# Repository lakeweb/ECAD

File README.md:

ECAD - Edit Schematics and PC Boards as well as manage projects and libraries from other CAD software.

So far, there are no editing features. The work is on creating a good foundation for CAD. Being able to handle objects easaly and having the UI in place comes first. VS2017 is required. The older compilers are not capable of building the parsers. MS is always behind the C++ language evolution.

Code of interest:
XMLSettingsStore derived from CSettingsStore and the use of pugixml. Find that in HEWinApp.cpp. I don't care for using the registry to store so much information. It should go in the appddata of the user. This will also make it easier to change profiles around.

pugixml wrapper:
In xml.h. Previously I had been using a crusty and bloated vesrsion of an XML wrapper around TinyXML. Tiny was hiden in that implamentation. It as worked fine for me for many years, but it was time to move on. The objective of this new pugi wrapper is to keep all of pugi exposed. But to make its use as a application database much easier. The use is already sprinkled about this app. It started with the XMLSettingsStore.

12/23/2018
BXL parser moved to lib.
Deleted old spirit::qi code.
Made it so recent file load won't crash on bad paths.
Found a lot of header dependencies beyond the repository fixes and depreciated std::tstring stuff.

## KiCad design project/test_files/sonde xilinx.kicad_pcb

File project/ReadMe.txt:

now using pugi xml...

MIlling and screen drawing................................

Geometry.h
	bases of 2D Cartesian points using
	boost geometry.
	support for transformations, rotations, mirroring, etc...

object.h
	primitive objects for milling and drawing
	a base class: BaseItem and containers use SP_BaseItem
		shared pointers..

Drawing.h
	support for drawing objects.

DrawingObect : top level container for drawing
	wrapper for object_set_t called only ItemSet for now.

ItemSet
	owns asp_obj_vect_t
	which is a vector of shared pointers SP_BaseItem

11/27/2018
	polygons are supported. They can be open, and/or, they can be filled.
	An ItemSet stored as a base object will not be considered a polygon. This may change.
	But if an ItemSet is stored in an ItemSet, it will be treated as a polygon.

	So far, the fill is a 

...........................................................................
The Tiny Parse
...........................................................................
boost::geometry does not support curved lines much less in a line string.
So each polygon is stored on a ItemSet.

			//<POLYGON pos = '15.00000,15.00000' style = '4' fill = '1'>
			//	<POINT pos = '0.00000,0.00000' arc = '0' / >
			//create an object for each polygon to preserve tiny objects.
			//geometry does not support curves in a linestring so....

Note that CppSQLite3U is rather unusable. The only reason it is in here is for tinylib
	it will be updated.....

On the local system, symlinks are set for:
folder: <include/xml.h>
file: <BXLReader/BXL_Component.h>

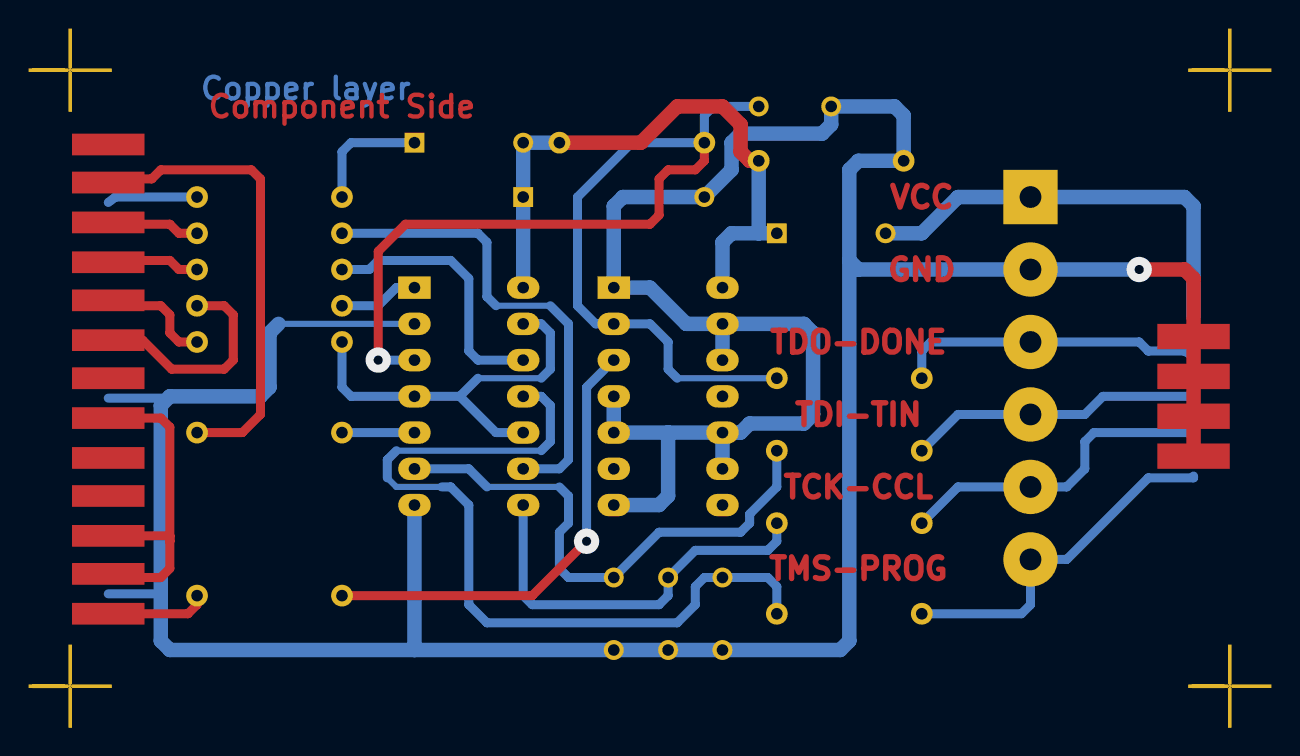
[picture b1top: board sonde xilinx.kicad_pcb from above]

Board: 2 copper layers, 29 parts (0 on the bottom side), 26 nets.

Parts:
C1: 1uF; CP5
C2, C3, C4, C5: 100pF; C2
D1, D2: BAT46; D3
J1: DB25MALE; DB25M_CI
J2: DB9MALE; DB9M_CI_INVERT
MIRE: *; MIRE
MIRE#2, MIRE#3, MIRE#4: *; MIRE
P1: CONN_6; bornier6
R1, R6, R7, R8, R9, R10, R11, R12, R13, R14: 100; R4
R2: 5,1K; R4
R4: 47; R4
R5: 1K; R4
U1, U2: 74LS125; 14DIP-ELL300

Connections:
/CLK-D1: J1.3, R10.2
/CTRL-D3: J1.5, R8.2
/DONE-SELECT*: J1.13, R4.2
/PWR_3,3-5V: D2.1, J2.1, P1.1
/TCK-CCLK: J2.4, P1.5, R12.1
/TD0-DONE: J2.2, P1.3, R14.1
/TD0-PROG-D4: J1.6, R6.2
/TDI-DIN: J2.3, P1.4, R11.1
/TDI-DIN-D0: J1.2, R7.2
/TMS-PROG: J2.5, P1.6, R13.1
/TMS-PROG-D2: J1.4, R9.2
/VCC_SENSE-ERROR*: J1.15, R1.2
GND: C1.2, C2.2, C3.2, C4.2, C5.2, J1.20, J1.25, J2.6, J2.7, J2.8, J2.9, P1.2, R5.2, U1.2, U1.7, U2.1, U2.4, U2.5, U2.7, U2.9, U2.10, U2.12, U2.13
unnamed: J1.8, J1.11, J1.12
unnamed: D1.2, R1.1
unnamed: R4.1, U2.3
unnamed: R7.1, U1.5
unnamed: R10.1, U1.9
unnamed: R6.1, U1.1
unnamed: R9.1, U1.12
unnamed: R8.1, U1.4, U1.10, U1.13
unnamed: C4.1, R13.2, U1.11
unnamed: C2.1, R11.2, U1.6
unnamed: C5.1, R12.2, U1.8
unnamed: C3.1, R2.2, R14.2, U1.3, U2.2
VCC: C1.1, D1.1, D2.2, R2.1, R5.1, U1.14, U2.14

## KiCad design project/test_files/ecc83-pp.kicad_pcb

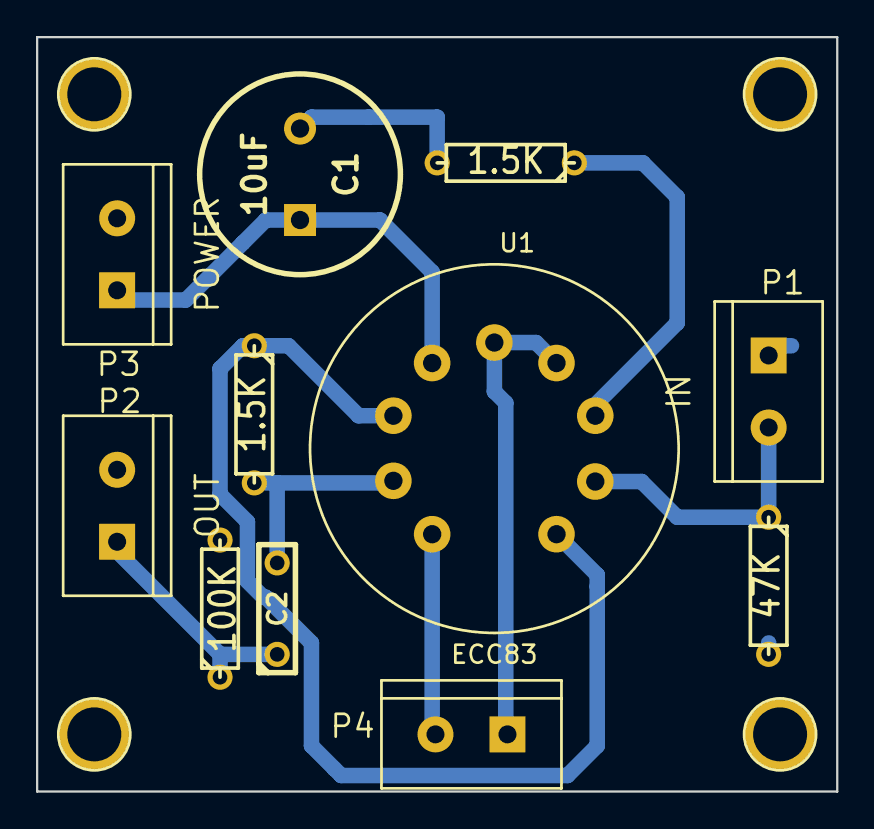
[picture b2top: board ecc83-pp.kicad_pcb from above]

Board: 2 copper layers, 44.5 x 41.9 mm, 15 parts (0 on the bottom side), 9 nets.

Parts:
C1: 10uF; C2V10
C2: 680nF; C2
P1: IN; bornier2
P2: OUT; bornier2
P3: POWER; bornier2
P4: CONN_2; bornier2
P5, P6, P7, P8: CONN_1; 1pin
R1, R2: 1.5K; R3
R3: 100K; R3
R4: 47K; R3
U1: ECC83; VALVE-ECC-83-1

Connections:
GND: C1.2, P1.1, P2.2, P3.2, R2.2, R3.2, R4.2
unnamed: C1.1, P3.1, U1.6
unnamed: C2.1, P2.1, R3.1
unnamed: C2.2, R1.2, U1.8
unnamed: P1.2, R4.1, U1.2
unnamed: P4.1, U1.4, U1.5
unnamed: P4.2, U1.9
unnamed: R1.1, U1.1, U1.7
unnamed: R2.1, U1.3

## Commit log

2018-12-20 First commit
    removing delete
2018-12-21 new file: LICENSE.md modified: README.md
2019-07-27 New commit
